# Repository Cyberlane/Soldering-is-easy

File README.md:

Soldering is easy!
==================

Schematics and designs for the Soldering is easy PCBs.

The basic 6 step guide (as seen at Brighton Mini Maker Faire 2013)  can be found here :
https://docs.google.com/document/d/1fZSY74wyp0Sk4oQom81q0h3l2oE5rRqwzkg6VrLCVWA/edit?usp=sharing

A more detailed step by step guide (with pictures) is available here : https://github.com/Cyberlane/Soldering-is-easy/blob/master/Tutorial.md

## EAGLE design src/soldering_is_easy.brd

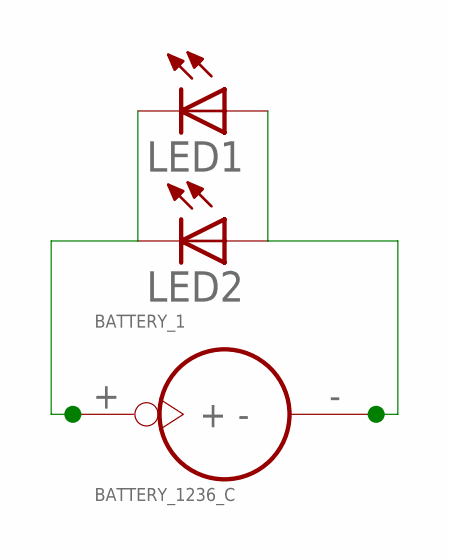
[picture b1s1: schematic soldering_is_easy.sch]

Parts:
BATTERY_1: BATTERY_1236_C
LED1, LED2: LED5MM

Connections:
unnamed: BATTERY_1.+, LED1.K (C), LED2.K (C)
unnamed: BATTERY_1.-, LED1.A, LED2.A

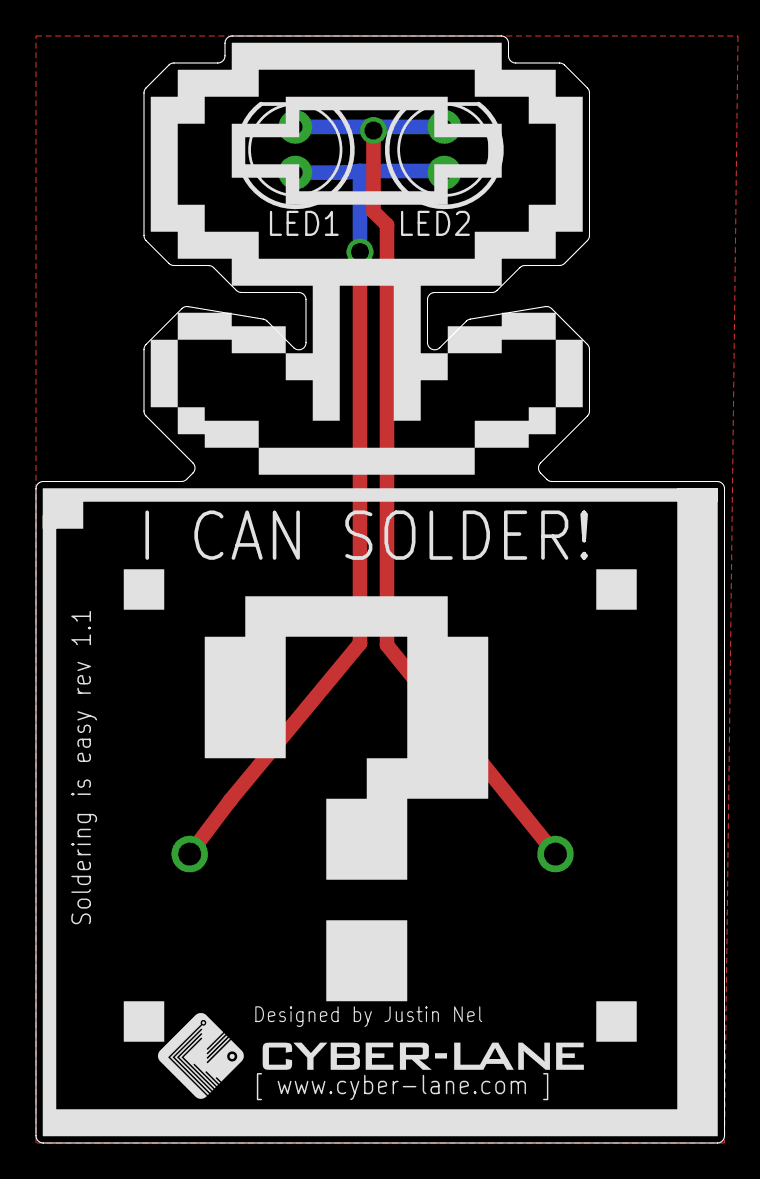
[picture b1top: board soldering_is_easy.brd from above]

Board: 2 copper layers, 38.2 x 61.5 mm, 3 parts (1 on the bottom side), 2 nets.

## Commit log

2013-08-10 First commit, rev 1 complete
2013-08-10 Cropped the board render
2013-08-13 Create gh-pages branch via GitHub
2013-08-27 Added scanned image of circuit board
2013-08-27 Extra picture of PCB
2013-09-06 Tutorial images
2013-09-06 Tweaked some images
2013-09-08 Renamed the tutorial images accordingly
2013-09-08 Cropped and scaled the tutorial images
2013-09-08 Referenced images for tutorial
2013-09-08 Step 1 - your kit
2013-09-08 Extra line breaks for Step 1
2013-09-08 Step 2
2013-09-08 Step 3
2013-09-08 Step 4
2013-09-08 Step 5
2013-09-08 Fixed some grammar and typos
2013-09-08 Fixed another minor typo
2013-10-04 gerbers for Hackvana
2013-10-04 rev 1.1
2013-10-04 Moved Battery Holder text slightly
2013-10-04 Updated gerbers for rev 1.1
2013-10-06 Removed tmp files
2013-11-17 How to solder an LED - coming soon
2013-11-27 Rev 1.2 - added ground planes
2013-12-08 Updated tutorial to link to wiki

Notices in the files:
parts and their libraries:
SparkFun-LED: Licensing: CC v3.0 Share-Alike You are welcome to use this library for commercial purposes.
